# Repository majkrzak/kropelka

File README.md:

kropelka
========

Fluid level ISM band radio sensor.

Introduction
------------

Aim of the project was to utilise the cc1101 board I recently acquired. Because of the last events in my neighbourhood, I came up with idea of creating the sensor detecting water level above the threshold.

Electronic Parts
-----

### ATtiny13A
Atmel picoPower 8-Bit AVR microcontroller.

### E07 M1101-SMA
EBYTE CC1191 Wireless Module.

### DFR0579
DFRobot Solar Power Manager Micro.

### Solar Panel
DFRobot 2V 160mA Solar Panel.

### Lipo battery
Akyga Li-Pol cell 190mAh 1S 3,7V

### CMW55
Magnetic fluid level sensor.

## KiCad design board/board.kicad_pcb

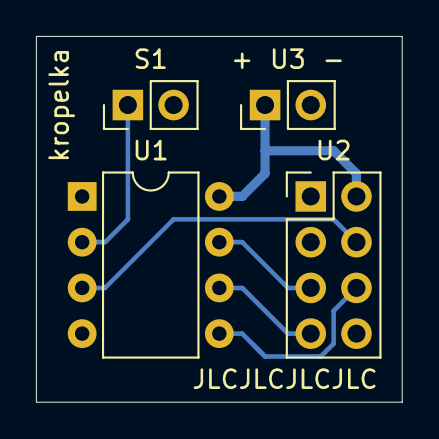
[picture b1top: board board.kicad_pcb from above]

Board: 2 copper layers, 20.3 x 20.3 mm, 4 parts (0 on the bottom side), 7 nets.

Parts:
S1: Float_Switch; PinHeader_1x02_P2.54mm_Vertical
U1: ATtiny13A-PU; DIP-8_W7.62mm
U2: E07-M1101D
U3: DFR0579; PinHeader_1x02_P2.54mm_Vertical

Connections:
GND: S1.2, U1.4, U2.1, U3.2
unnamed: S1.1, U1.2
unnamed: U1.3, U2.4
unnamed: U1.5, U2.6
unnamed: U1.6, U2.7
unnamed: U1.7, U2.5
VCC: U1.8, U2.2, U3.1

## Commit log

2021-08-19 Add readme
2021-08-19 Add base build script
2021-08-19 Add main stub
2021-08-19 Clean up build script
2021-08-20 Add SPI library
2021-08-20 Add CC1101 library
2021-08-21 Parametrize radio configuration
2021-08-21 Add channel bandwidth configuration
2021-08-28 Add cc1101 initialization
2021-08-28 Fix lining flags
2021-08-28 Add SPI timing
2021-08-28 Fix SPI
2021-08-28 Add first test transmission\n rtl_433 -X "name=kropelka,modulation=OOK_MC_ZEROBIT,short=844,l=0,r=1672,preamble=aaabba,get=test:@0:{32}"
2021-08-29 Implement watchdog sleep
2021-08-29 Set clock prescaler to 0
2021-08-29 Separate watchdog management
2021-08-29 Implement radio sleep\nPATABLE have to be recreated after waking up
2021-08-29 Add sane wakeup
2021-08-29 Reduce spi timings
2021-08-29 Add sensor state check
2021-08-30 Add kicad library with E07-M1101D board
2021-08-30 Add Floating Switch to kicad Library
2021-08-30 Add DF robot solar micro symbol
2021-08-30 Update E07 footprint
2021-08-31 Add Kicad project with first board version
2021-08-31 Add silkscreen +/- markings
2021-08-31 Small schematic fixes
2021-08-31 Set JLCPCB export settings
2021-09-10 Add UUID and counter to sended packet
2021-09-10 Fix bit value of syncmode
2021-09-10 Add case schema
2021-09-18 Rework case
2021-09-18 Add rants
2021-09-18 Add holes
2021-09-18 Add cover
2021-09-20 Rework cover, add MasterSketch
2021-09-20 Model the case
2021-09-20 Rename the case
2021-09-20 Add generated assets
2021-12-01 Add readme draft
